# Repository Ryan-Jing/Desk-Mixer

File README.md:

# Desk-Mixer

A desk-top two-deck music mixer. Two tracks play at once; physical faders, knobs and buttons let
you crossfade, filter and vary the tempo of each while an LCD shows what is loaded. A companion
app on your laptop puts music on it.

Built on a **Teensy 4.1** on a custom PCB.

---

## Repository

| Path | What |
|---|---|
| [`Firmware/`](Firmware/) | Firmware — PlatformIO, C++ |
| [`App/`](App/) | Companion app — Python + PySide6 |
| [`Electrical/`](Electrical/) | Schematics and board — KiCad |
| [`Docs/`](Docs/) | Engineering source of truth |
| [`Tools/`](Tools/) | Cross-project code generation and checks |

## Hardware at a glance

| Function | Part |
|---|---|
| MCU | Teensy 4.1 — i.MX RT1062, 600 MHz Cortex-M7 |
| Audio codec | SGTL5000 → 3.5 mm jack, via I2S1 |
| Bluetooth audio | BM83SM1-00TA, fed digitally over I2S2 |
| Storage | microSD, native 4-bit SDIO |
| Power | USB-C → TUSB320 CC → TPS259251 eFuse → TPSM82903 buck |

Both I2S peripherals run at once, so the analog and Bluetooth outputs are independent and
Bluetooth needs no analog round trip.

## How music gets on it

```
Spotify playlist  ──►  metadata only (titles, artists, ISRC)
                            │
                    TrackResolver  ──►  a local audio file you own
                            │
                    ffmpeg  ──►  16-bit 44.1 kHz stereo WAV
                            │
                    USB serial  ──►  SD card  /library/<playlist>/<track>.wav
```

Spotify is never asked for audio — that is a deliberate boundary, not a gap.
See [ADR 0004](Docs/decisions/0004-track-resolver.md).

## Quick start

```sh
# firmware
cd Firmware
pio run -e teensy41            # build
pio test -e native             # host unit tests (once suites exist)

# companion app
cd ../App
python3 -m venv .venv && .venv/bin/python -m pip install -e '.[dev]'
.venv/bin/ruff check .         # tests and type checks once modules exist
```

Enable the shared pre-push gate once:

```sh
git config core.hooksPath .githooks
```

## Documentation

| Read this | For |
|---|---|
| [architecture.md](Docs/architecture.md) | how the three pieces fit together |
| [pinout.md](Docs/pinout.md) | the Teensy pin map — source of truth |
| [audio-architecture.md](Docs/audio-architecture.md) | the audio graph, timing and CPU budget |
| [protocol.md](Docs/protocol.md) | the app ↔ device wire protocol |
| [sd-layout.md](Docs/sd-layout.md) | what lives on the card |
| [testing.md](Docs/testing.md) | the test strategy, and what it deliberately does not cover |
| [decisions/](Docs/decisions/) | why things are the way they are |
| [claude-setup-guide.md](Docs/claude-setup-guide.md) | configuring Claude Code for this repo |

## Two things worth knowing up front

**USB audio out does not work.** The USB-C on the host header has no software path: `USBHost_t36`
has no USB Audio Class driver, none exists for Teensy, and the host stack's isochronous support is
unreliable. The firmware reports that output as unavailable rather than pretending.
[ADR 0005](Docs/decisions/0005-usb-host-audio.md) covers the alternatives.

**The BM83 must be switched to Host Mode** with Microchip's Config Tool before its UART responds
to anything. It ships in Embedded Mode. [ADR 0003](Docs/decisions/0003-bluetooth-bm83.md).

## Status

| Area | State |
|---|---|
| Firmware | **scaffolding only** — bare superloop in `main.cpp`, builds clean. Module breakdown deliberately undecided |
| Companion app | **scaffolding only** — design and build order in [`App/README.md`](App/README.md) |
| Wire protocol | **specified**, with generators for both sides written but parked until each side picks a layout |
| Display | **panel not yet chosen** |
| Control surface | provisional pin map; `Interface.kicad_sch` is empty |
| PCB | 36 footprints placed, **no routing yet** |

Firmware is written by Ryan, with the architecture worked out collaboratively — integration notes
per subsystem are in [`Firmware/README.md`](Firmware/README.md). The app is unbuilt; its design and
a step-by-step build order are in [`App/README.md`](App/README.md).

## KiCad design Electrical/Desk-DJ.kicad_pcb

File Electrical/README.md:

# Desk-Mixer — PCB

KiCad 10 project (`Desk-DJ`). **Four-layer**, 1.6 mm FR4.

> **This directory is hand-edited in KiCad.** Nothing else in this repository modifies it, and
> tooling should not either — editing `.kicad_sch` or `.kicad_pcb` as text corrupts UUIDs and net
> linkage.

## Sheets

| Sheet | State |
|---|---|
| `USB_Input.kicad_sch` | USB-C power input: `USBLC6-2SC6` ESD → `TUSB320` CC → eFuse |
| `Power.kicad_sch` | `TPS259251` eFuse → `TPSM82903` buck → +3V3. Most complete sheet |
| `Microcontrollers.kicad_sch` | Teensy 4.1 pin budget assigned; BM83 placed but unwired |
| `Audio_IO.kicad_sch` | SGTL5000 I2S/I²C/headphone out, `SJ1-3525N` jack. No power section yet |
| `LCD.kicad_sch` | **empty** |
| `Interface.kicad_sch` | **empty** |

The board has 36 footprints imported and **no tracks, pours or outline**.

Four layers rather than two: the stackup has to give an uninterrupted ground plane under the USB
differential pairs and both I2S MCLK lines. Those are 11.29 MHz square waves running near the
analog section, and on two layers you end up choosing which of impedance control or analog
isolation to compromise.

## What firmware depends on

The pin map lives in [`Docs/pinout.md`](../Docs/pinout.md) and
`Firmware/include/config.h`, both derived from this schematic.

**If they disagree with the schematic, the schematic wins.** Flag the discrepancy rather than
editing either side silently.

## BM83 — what the board must provide

Use **`BM83SM1-00TA`** (Audio Transceiver firmware, A2DP source), not `-00AB` (speaker linking).

Beyond I2S2 and the UART, three control lines need Teensy GPIOs: `MFB` (26), `RST_N` (43) and
`P3_4` (31). `P3_4` and `RST_N` are what let the Teensy put the module into flash mode and act as a
serial relay for Microchip's PC tools — which is how a soldered module stays recoverable without a
programming header or USB traces to the module.

No copper, traces or components beneath the module's PCB antenna.

## Open items

A read of the netlist on 2026-08-26 turned up several things worth checking next time this is
open — an I²C net-name mismatch, a power-button symbol that is actually an LDO, the SGTL5000's
missing power section, and the unwired BM83 among them. They are recorded in
[ADR 0006](../Docs/decisions/0006-electrical-review.md) as reference, not as a task list.

## Portability warning

Every non-stock symbol and footprint resolves through the **global** KiCad library table at
`~/Local/System-Local/Packages/KiCad/…`, outside this repository. Cloning the repo on another
machine will break all of them. Vendoring the project libraries under this directory would fix it.

## Ignored files

`.gitignore` excludes KiCad's per-user state: `*.kicad_prl`, `fp-info-cache`, `*-backups/`,
`_restore_backup_*/`, lock files, and `.history/`. That last one is KiCad 10's Local History,
which keeps its **own nested git repository** — it was previously picked up as a gitlink with no
`.gitmodules`, which breaks `git submodule status`.

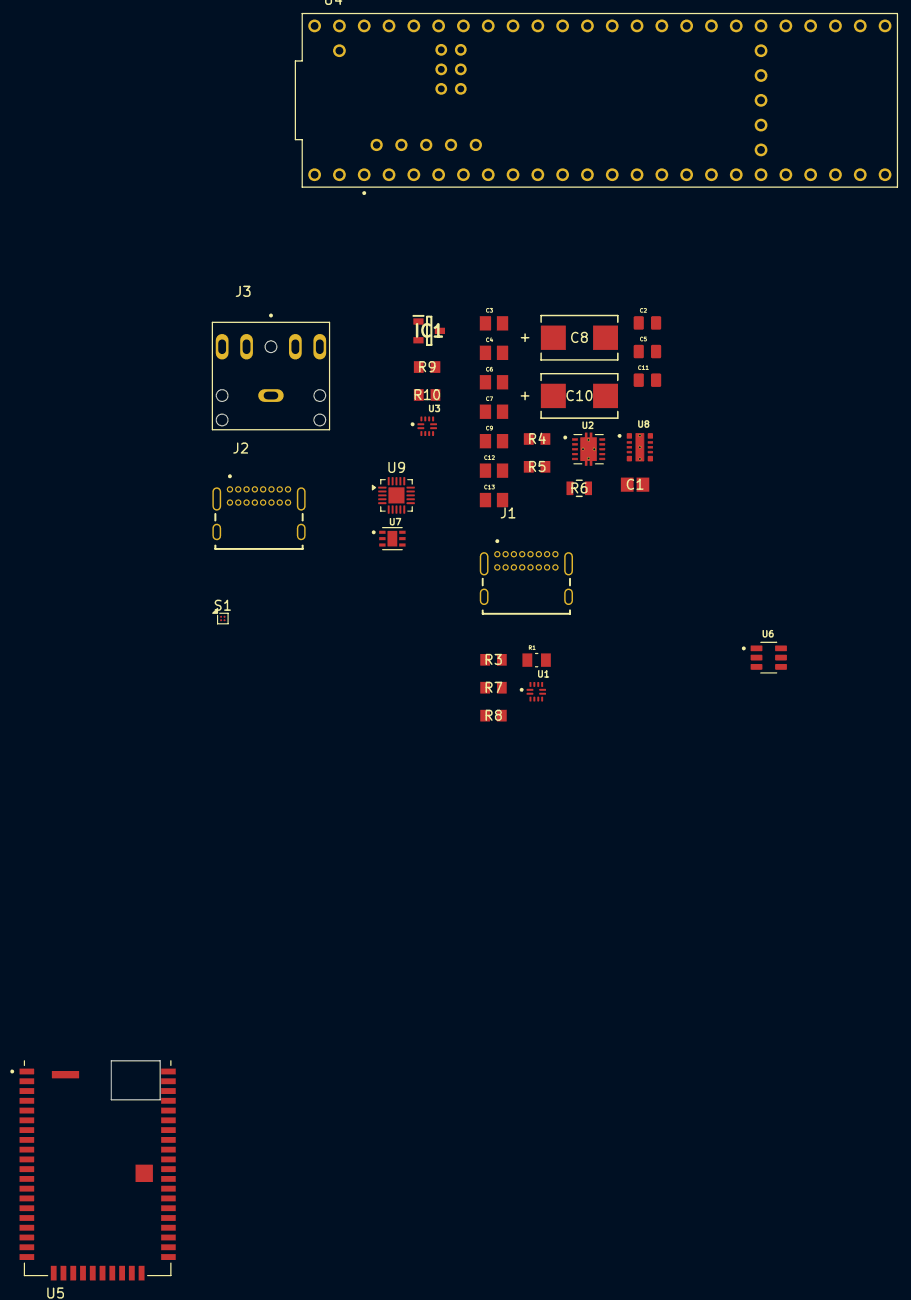
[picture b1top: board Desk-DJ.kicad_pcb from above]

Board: 2 copper layers, 36 parts (0 on the bottom side), 35 nets, no tracks yet.

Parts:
C1: C0805C102K5RACTU; CAPC220145_88N_KEM
C2, C5, C11: CL21B105KBFNNNE; CAPC2012X135N
C3, C6, C12: C0805C473K5RACTU; CAPC2012X88N
C4, C7, C9, C13: C0805C100JDGACTU; CAPC2012X140N
C8, C10: T520D227M010ATE040; CAPMP7.6X4.3_3.1N_KEM
IC1: AP7313-18SRG-7; SOT96P240X135-3N
J1, J2: USB4085-GF-A_REVA4; GCT_USB4085-GF-A_REVA4
J3: SJ1-3525N; CUI_SJ1-3525N
R1: RMCF0805ZT0R00; RESC2012X65N
R3: CRCW0805887KFKEA; RC0805N_VIS
R4, R5: RC0805FR-07100KL; RC0805N_YAG
R6: CRCW0805560KFKEA; RES_CRCW_0805
R7, R8, R9, R10: ERJ-6GEYJ473V; RC0805N_PAN
S1: TL3365AF180QG; WLCSP-4_0.64x0.64mm_Layout2x2_P0.35mm
U1, U3: TUSB320RWBR; IC_TUSB320RWBR
U2: TPS259251DRCT; VREG_V62_16624-01YE
U4: DEV-16771; MODULE_DEV-16771
U5: BM83SM1-00TA; XCVR_BM83SM1-00TA
U6: USBLC6-2SC6; SOT95P280X145-6N
U7: TPS2552DRVR; SON65P200X200X80-7N
U8: TPSM82903SISR; IC_TPSM82903SISR
U9: SGTL5000XNLA3; QFN-20-1EP_3x3mm_P0.4mm_EP1.65x1.65mm

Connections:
3V3_PG: U4.34 (RX8), U8.6 (PG)
+3.3V: C10.1, C11.2, C12.1, C13.1, R8.1, R10.1, U1.12 (VDD), U3.12 (VDD), U8.9 (VOUT), U8.10 (VOUT__1)
+5V: C5.2, C6.1, C7.1, C8.1, C9.1, R5.2, U2.6 (VOUT-2), U2.7 (VOUT-1), U2.8 (VOUT), U4.5V, U4.VIN, U4.VUSB, U7.6 (IN), U8.1 (VIN), U8.2 (VIN__1), U8.3 (EN), U8.4 (MODE/S-CONF)
GND: C1.2, C2.1, C3.2, C4.2, C5.1, C6.2, C7.2, C8.2, C9.2, C10.2, C11.1, C12.2, C13.2, J1.A1 (GND), J1.A12 (GND), J1.B1 (GND), J1.B12 (GND), J1.S1 (SHELL), J1.S2 (SHELL), J1.S3 (SHELL), J1.S4 (SHELL), J2.A1 (GND), J2.A12 (GND), J2.B1 (GND), J2.B12 (GND), J2.S1 (SHELL), J2.S2 (SHELL), J2.S3 (SHELL), J2.S4 (SHELL), R1.1, R4.1, R6.2, R7.2, R9.2, U1.3 (PORT), U1.10 (GND), U3.10 (GND), U4.GND1 (GND), U4.GND2 (GND__1), U4.GND3 (GND__2), U4.GND4 (GND__3), U4.GND5 (GND__4), U4.USB_GND1 (USB_GND), U4.USB_GND2 (USB_GND__1), U6.2 (GND), U8.11 (GND), U9.21 (GND)
I2C_SCL: U3.8 (SCL/OUT2), U9.19 (CTRL_CLK)
I2C_SDA: U3.7 (SDA/OUT1), U4.18 (A4), U9.18 (CTRL_DATA)
I2S1_BCLK: U4.21 (A7), U9.15 (I2S_SCLK)
I2S1_LRCLK: U4.20 (A6), U9.14 (I2S_LRCLK)
I2S1_MCLK: U4.23 (A9), U9.13 (SYS_MCLK)
I2S1_TEENSY_IN: U4.7 (RX2), U9.16 (I2S_DOUT)
I2S1_TEENSY_OUT: U4.8 (TX2), U9.17 (I2S_DIN)
unnamed: J1.A5 (CC1), U1.1 (CC1)
unnamed: J1.B5 (CC2), U1.2 (CC2)
unnamed: J1.A7 (DN1), J1.B7 (DN2), U6.3 (D-_IN)
unnamed: J1.A6 (DP1), J1.B6 (DP2), U6.1 (D+_IN)
unnamed: J2.A5 (CC1), U3.1 (CC1)
unnamed: J2.B5 (CC2), U3.2 (CC2)
unnamed: R8.2, U1.5 (ADDR)
unnamed: R1.2, U1.9 (ID)
unnamed: R3.1, U1.4 (VBUS_DET)
unnamed: R7.1, U1.11 (~EN_N)
unnamed: C1.1, U2.1 (DV/DT)
unnamed: R5.1, R6.1, U2.2 (EN/UVLO)
unnamed: R4.2, U2.10 (ILIM)
unnamed: R9.1, U3.5 (ADDR)
unnamed: U3.9 (ID), U7.4 (~EN)
unnamed: R10.2, U3.3 (PORT)
unnamed: J3.2, U9.4 (HP_L)
unnamed: J3.3, U9.1 (HP_R)
unnamed: J3.1, U9.2 (HP_VGND)
TEENSY_3V3_OUT: U4.3.3V_1 (3.3V), U4.3.3V_2 (3.3V__1), U4.3.3V_3 (3.3V__2)
USBC_5V_FLT: U4.31 (CTX3), U7.3 (~FAULT)
USBC_AUDIO_DET: U3.6 (~INT_N/OUT3), U4.30 (CRX3)
USBC_AUDIO_EN: U3.11 (~EN_N), U4.35 (TX8)
VBUS: C2.2, C3.1, C4.1, J1.A4 (VBUS), J1.A9 (VBUS), J1.B4 (VBUS), J1.B9 (VBUS), J2.A4 (VBUS), J2.A9 (VBUS), J2.B4 (VBUS), J2.B9 (VBUS), R3.2, U2.3 (VIN-1), U2.4 (VIN), U2.5 (VIN-2), U6.5 (VBUS), U7.1 (OUT)
